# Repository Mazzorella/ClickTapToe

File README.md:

# ClickTapToe

ClickTapToe is a custom foot-operated mouse for people who need to reduce repetitive hand and arm movement. The goal is to move common mouse actions away from the hands by using foot pedals for clicking, a large foot-driven scroll wheel, and a separate mouse pointer module.

This repository contains the firmware, hardware notes, and project documentation for ClickTapToe. The current firmware target is a Seeed Studio XIAO nRF52840 / XIAO BLE running as a USB HID mouse with ZMK. Bluetooth is disabled for the ClickTapToe firmware build.

## Current Status

The current firmware supports USB mouse clicks from external pedals, USB vertical scrolling from the input hub scroll wheel, and pointer movement from the mouse pointer module:

- Left click on the first pedal input
- Right click on the second pedal input
- Vertical scroll from the AS5600 magnetic angle sensor connected to the input hub scroll wheel
- Pointer movement from the PMW3610 sensor in the mouse pointer module
- `D2` and `D3` remain spare/test inputs and are not exposed as production pedal jacks on the current input hub PCB

PMW3610 pointing support is active for the current firmware target.

## Hardware Overview

ClickTapToe is built from two custom electronics modules plus external pedals:

- The input hub contains the XIAO nRF52840 controller, USB connection, external pedal TS jacks, RJ45 pointer connection, and a large foot-operated scroll wheel coupled to an AS5600 magnetic angle sensor.
- The mouse pointer module is shaped like a slipper, houses a PMW3610 pointing sensor, and connects to the input hub over RJ45 with a short Ethernet cable.
- The pedals are premade external pedals connected to the input hub so higher-quality parts can be used and the project is easier to reproduce.

See [HARDWARE.md](HARDWARE.md) for the current pin map and hardware notes.
For a public-facing hardware overview with embedded board previews, open the
[ClickTapToe Hardware Viewer](https://mazzorella.github.io/ClickTapToe/).

| Board | Source | KiCanvas preview |
| --- | --- | --- |
| Input hub | [hardware/input-hub/](hardware/input-hub/) | [Open preview](https://mazzorella.github.io/ClickTapToe/hardware/input-hub/kicanvas.html) |
| Mouse pointer | [hardware/mouse-pointer/](hardware/mouse-pointer/) | [Open preview](https://mazzorella.github.io/ClickTapToe/hardware/mouse-pointer/kicanvas.html) |

## Repository Layout

- `.github/workflows/build.yml` runs the upstream ZMK user-config build workflow.
- `build.yaml` defines the firmware build matrix.
- `config/west.yml` tracks upstream ZMK and imports ZMK's west manifest.
- `zephyr/module.yml` declares this repository as the `zmk-keyboard-clicktaptoe` module and exposes its board, devicetree binding, Kconfig, and driver files.
- `boards/shields/clicktaptoe/` contains the ClickTapToe shield definition, overlay, metadata, and default keymap.
- `Makefile` wraps the local `west build` command for Docker/devcontainer use.
- `hardware/` contains the input hub and mouse pointer KiCad source files.
- `docs/` is reserved for assembly, usage, and release documentation.

## Build Target

The active firmware target is:

```yaml
board: xiao_ble//zmk
shield: clicktaptoe
artifact-name: clicktaptoe_xiao_usb_zmk
```

## Flashing

1. Build the firmware with GitHub Actions or a local ZMK toolchain.
2. Put the XIAO BLE into bootloader mode so it mounts as a UF2 drive.
3. Copy the generated `clicktaptoe_xiao_usb_zmk.uf2` file onto the mounted drive.
4. After the board reboots, connect it to the host over USB.

## Hardware Test

Use a safe desktop target for click testing, such as an empty Finder window or browser page.

- Short physical `D0` to `GND`; the host should receive a left click.
- Short physical `D1` to `GND`; the host should receive a right click.
- Rotate the AS5600 scroll wheel; the host should receive vertical scroll events.
- Move the mouse pointer module over a surface; the host pointer should move smoothly in the same direction.
- Test the PMW3610 once through the RJ45 cable path; pointer response should match the direct breadboard wiring test.
- Leave the AS5600 magnet away from the sensor once as a negative test; the host should not scroll continuously.
- Verify `D2` and `D3` only as spare/test GPIOs if they are wired for bring-up.

If macOS does not immediately recognize the updated HID device, unplug and reconnect the XIAO BLE.
If an old Bluetooth name appears after flashing, remove the cached Bluetooth entry from the host. This firmware build disables ZMK BLE.
If the PMW3610 does not move the pointer after flashing, power-cycle the XIAO once. The input hub physically routes PMW3610 `nRESET` on XIAO `D6` / RJ45 pin 8, but the current firmware still relies on SPI/software reset and does not drive that reset line yet.

## Local Build Notes

This repository is both a ZMK config repository and a ZMK module. Local builds should make the repository visible to ZMK as the config path and as an extra module so the custom `clicktaptoe` shield can be discovered.

The preferred local workflow is to build from a ZMK Docker/devcontainer environment and use this repository's `Makefile`.

One common local layout is to keep this repository next to a ZMK firmware checkout:

```text
projects/
  zmk/
  zmk-pmw3610-driver/
  ClickTapToe/
```

Open the ZMK firmware checkout in VS Code:

```sh
code /path/to/projects/zmk
```

Then use **Dev Containers: Reopen in Container**. If using a devcontainer, bind mount this repository into the container and run the build commands from the ClickTapToe repository directory.

On the first devcontainer launch, initialize the Zephyr workspace from the ZMK checkout:

```sh
west init -l app/
west update
```

Restart the devcontainer after `west update` completes.

Clone the PMW3610 driver module where the `Makefile` can find it. In the default devcontainer layout:

```sh
git clone https://github.com/badjeff/zmk-pmw3610-driver /workspaces/zmk-pmw3610-driver
```

After that, run the build commands from this repository:

```sh
make build
```

To build and copy the generated UF2 into this repository's `firmware/` directory:

```sh
make uf2
```

The copied firmware path is:

```sh
firmware/clicktaptoe_xiao_usb_zmk.uf2
```

Build outputs are written under this repository's ignored `build/` directory,
not under ZMK's `app/` tree.

By default, the `Makefile` expects ZMK's app directory to be available at `../zmk/app`, which matches the sibling directory layout shown above. Override `ZMK_APP` if your checkout path differs:

```sh
make uf2 ZMK_APP=/path/to/zmk/app
```

The wrapped `west` command has this shape:

```sh
west build -d "/path/to/this-repo/build/clicktaptoe" -b "xiao_ble//zmk" -- \
  -DSHIELD=clicktaptoe \
  -DZMK_CONFIG="/path/to/this-repo/config" \
  -DZMK_EXTRA_MODULES="/path/to/this-repo;/path/to/zmk-pmw3610-driver"
```

By default, the `Makefile` expects the PMW3610 driver module at `../zmk-pmw3610-driver`. Override `PMW3610_MODULE` if your checkout path differs:

```sh
make uf2 PMW3610_MODULE=/path/to/zmk-pmw3610-driver
```

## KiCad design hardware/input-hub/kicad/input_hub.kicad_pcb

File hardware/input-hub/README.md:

# Input Hub Hardware

This folder contains source files and notes for the ClickTapToe input hub PCB.

The input hub is the central electronics board. It hosts the XIAO nRF52840,
connects to the computer over USB, receives the external pedal TS jacks,
connects to the mouse pointer board over RJ45, and interfaces with the AS5600
scroll sensor.

## XIAO Pin Test Plan

This validation plan keeps the existing click pedals on `D0`/`D1`, uses the
AS5600 scroll sensor on the `D4`/`D5` I2C bus, and leaves the PMW3610 SPI
signals unchanged.

| XIAO pin | Signal plan | Firmware status |
| --- | --- | --- |
| `D0` | Left click pedal | Implemented |
| `D1` | Right click pedal | Implemented |
| `D2` | Future footswitch / TTS / spare input | Test direct GPIO input, emits play/pause |
| `D3` | Future footswitch / TTS / spare input | Test direct GPIO input, emits volume up |
| `D4` | AS5600 I2C bus | Implemented as `&xiao_i2c` |
| `D5` | AS5600 I2C bus | Implemented as `&xiao_i2c` |
| `D6` | PMW3610 `nRESET` | Implemented as active-low hardware reset |
| `D7` | PMW3610 `MOTION` | Implemented as PMW3610 interrupt |
| `D8` / `P1.13` | PMW3610 `SCLK` | Implemented |
| `D9` / `P1.14` | PMW3610 `nCS` | Implemented |
| `D10` / `P1.15` | PMW3610 `SDIO` | Implemented |

## Mouse Pointer RJ45 Pinout

The mouse pointer connector is an 8P8C modular jack used for ClickTapToe sensor
wiring. It is not Ethernet. The input hub RJ45 wiring must match the mouse
pointer board exactly.

| RJ45 pin | Signal | Input hub side |
| --- | --- | --- |
| 1 | `VIN` / `3V3` | 3.3 V sensor power |
| 2 | `GND` | Ground |
| 3 | `SCLK` | PMW3610 SPI clock |
| 4 | `SDIO` | PMW3610 bidirectional SPI data |
| 5 | `nCS` | PMW3610 chip select |
| 6 | `GND` | Ground |
| 7 | `MOTION` | PMW3610 motion interrupt |
| 8 | `nRESET` | PMW3610 reset routed to XIAO `D6` |

Twisted pair grouping:

| Pair | RJ45 pins | Signals |
| --- | --- | --- |
| Pair 1 | 1-2 | `VIN` / `3V3` + `GND` |
| Pair 2 | 3-6 | `SCLK` + `GND` |
| Pair 3 | 4-5 | `SDIO` + `nCS` |
| Pair 4 | 7-8 | `MOTION` + `nRESET` |

Series resistors for `SCLK`, `SDIO`, `nCS`, and `nRESET` belong on the input hub
side. The mouse pointer board only adds a local 100 ohm series resistor on
`MOTION`, and the input hub provides the `MOTION` pull-up to `3V3`.

`MOTION` is active-low and is handled by firmware on XIAO `D7`; the board also
has a 10k pull-up to `3V3` on that line.
`nRESET` is present in the cable on RJ45 pin 8 and is driven by firmware on XIAO
`D6` during PMW3610 initialization and retry.

## Online Review

`kicanvas.html` embeds the schematic and PCB in KiCanvas for browser-based
review. If GitHub Pages is enabled from the repository root, the input hub
viewer is available at:

```text
https://mazzorella.github.io/ClickTapToe/hardware/input-hub/kicanvas.html
```

## Planned Layout

- `kicad/` for KiCad project source files
- `kicad/production/` for generated Gerbers, drill files, BOMs, and placement files

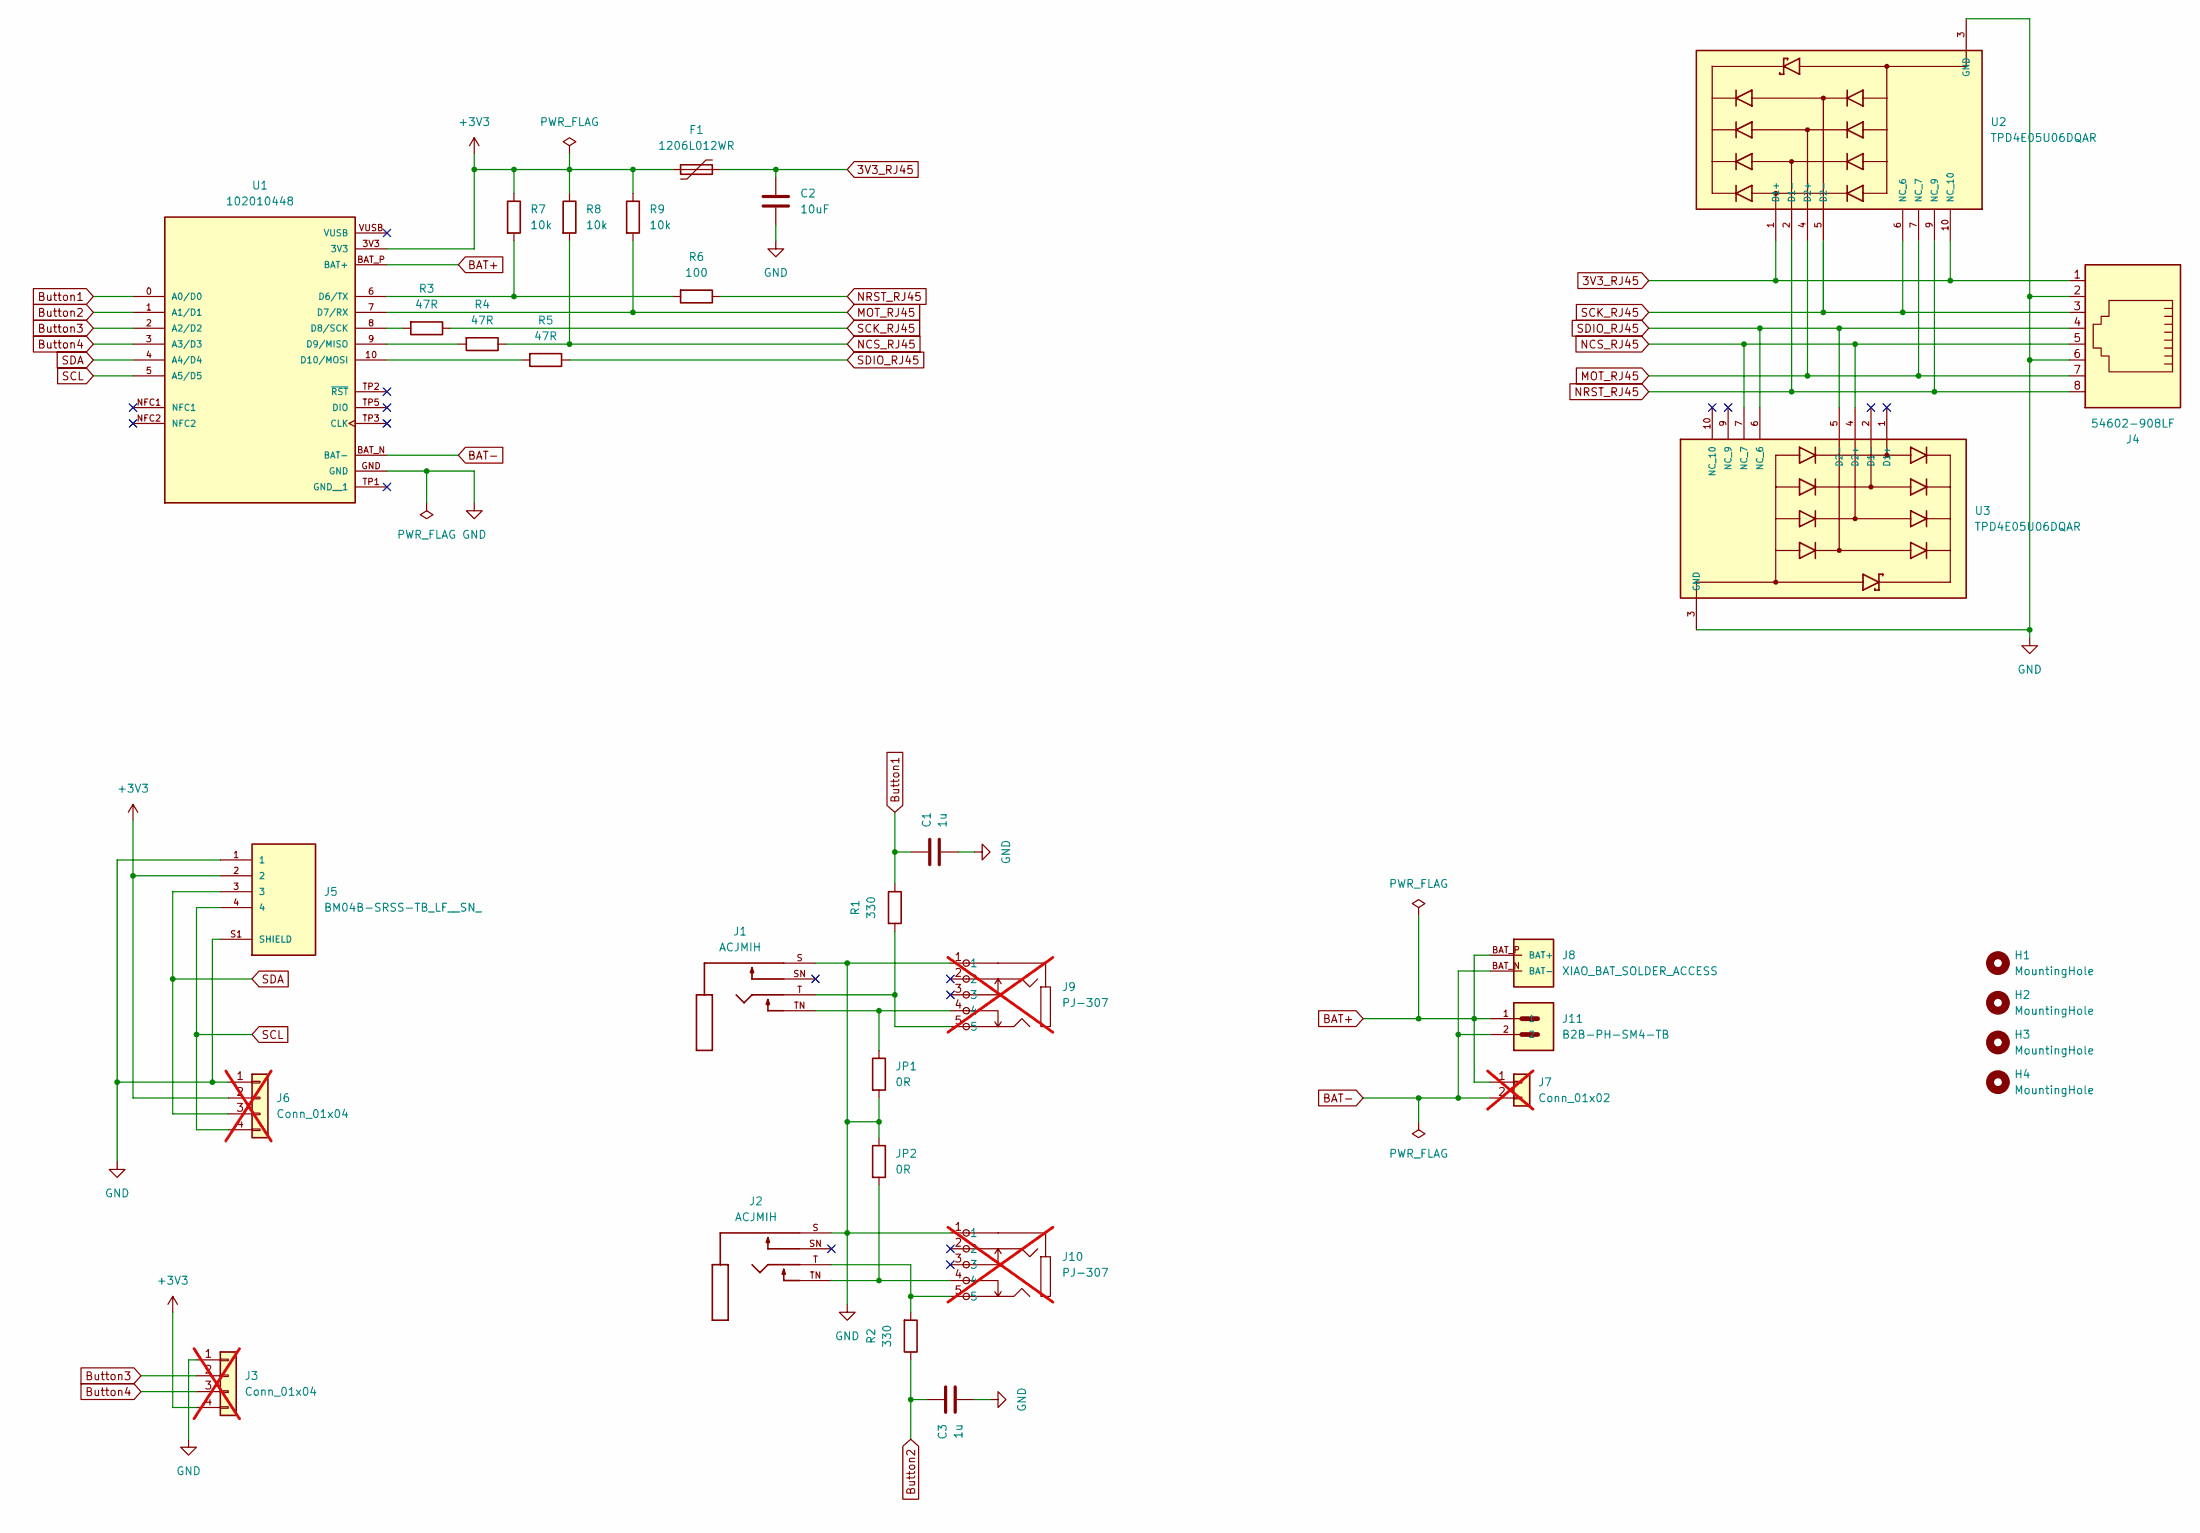
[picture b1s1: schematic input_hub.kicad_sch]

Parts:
C1, C3: 1u; C_0603_1608Metric; JLCPCB Part # C15849
C2: 10uF; C_0805_2012Metric; JLCPCB Part # C15850
F1: 1206L012WR; Fuse_1206_3216Metric; JLCPCB Part # C151160
H1, H2, H3, H4: MountingHole; MountingHole_3.2mm_M3_ISO14580
J1, J2: ACJMIH; AMPHENOL_ACJMIH; PARTREV 2; DigiKey_Part_Number 889-ACJM-IH-ND
J3, J6: Conn_01x04; PinHeader_1x04_P2.54mm_Vertical; not fitted
J4: 54602-908LF; RJ45_Amphenol_54602-x08_Horizontal; MFR. Part # 54602-908LF; Digi-Key MFR. Part # 54602-908LF
J5: BM04B-SRSS-TB_LF__SN_; JST_BM04B-SRSS-TB_LF__SN_; PARTREV N/A; JLCPCB Part # C160390
J7: Conn_01x02; PinHeader_1x02_P2.54mm_Vertical; not fitted
J8: XIAO_BAT_SOLDER_ACCESS
J9, J10: PJ-307; AUDIO-TH_PJ-307; MPN PJ-307; LCSC Part C2939173; not fitted
J11: B2B-PH-SM4-TB; JST_PH_B2B-PH-SM4-TB_1x02-1MP_P2.00mm_Vertical; MFR. Part # B2B-PH-SM4-TB(LF)(SN); JLCPCB Part # C160352
JP1, JP2: 0R; R_0603_1608Metric; JLCPCB Part # C21189
R1, R2: 330; R_0603_1608Metric; JLCPCB Part # C23138
R3, R4, R5: 47R; R_0603_1608Metric; JLCPCB Part # C23182
R6: 100; R_0603_1608Metric; JLCPCB Part # C22775
R7, R8, R9: 10k; R_0603_1608Metric; JLCPCB Part # C25804
U1: 102010448; MODULE_102010448; PARTREV 2022/08/18; Digi-Key MFR. Part # 102010448
U2, U3: TPD4E05U06DQAR; IC_TPD4E05U06DQAR; PARTREV N; JLCPCB Part # C138714

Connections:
3V3_RJ45: C2.2, F1.2, J4.1, U2.1 (D1+), U2.10 (NC_10)
+3V3: F1.1, J3.4, J5.2, J6.2, R7.1, R8.1, R9.1, U1.3V3
BAT+: J7.1, J8.BAT_P (BAT+), J11.1, U1.BAT_P (BAT+)
BAT-: J7.2, J8.BAT_N (BAT-), J11.2, U1.BAT_N (BAT-)
Button1: C1.2, R1.1, U1.0 (A0/D0)
Button2: C3.2, R2.1, U1.1 (A1/D1)
Button3: J3.2, U1.2 (A2/D2)
Button4: J3.3, U1.3 (A3/D3)
GND: C1.1, C2.1, C3.1, J1.S, J2.S, J3.1, J4.2, J4.6, J5.1, J5.S1 (SHIELD), J5.S2 (SHIELD), J6.1, J9.1, J10.1, JP1.2, JP2.1, U1.GND, U2.3 (GND), U2.8 (GND), U3.3 (GND), U3.8 (GND)
MOT_RJ45: J4.7, R9.2, U1.7 (D7/RX), U2.4 (D2+), U2.7 (NC_7)
NCS_RJ45: J4.5, R4.1, R8.2, U3.4 (D2+), U3.7 (NC_7)
NRST_RJ45: J4.8, R6.1, U2.2 (D1-), U2.9 (NC_9)
unnamed: J1.T, J9.5, R1.2
unnamed: J1.TN, J9.4, JP1.1
unnamed: J2.TN, J10.4, JP2.2
unnamed: J2.T, J10.5, R2.2
unnamed: R6.2, R7.2, U1.6 (D6/TX)
unnamed: R3.2, U1.8 (D8/SCK)
unnamed: R4.2, U1.9 (D9/MISO)
unnamed: R5.2, U1.10 (D10/MOSI)
SCK_RJ45: J4.3, R3.1, U2.5 (D2-), U2.6 (NC_6)
SCL: J5.4, J6.4, U1.5 (A5/D5)
SDA: J5.3, J6.3, U1.4 (A4/D4)
SDIO_RJ45: J4.4, R5.1, U3.5 (D2-), U3.6 (NC_6)

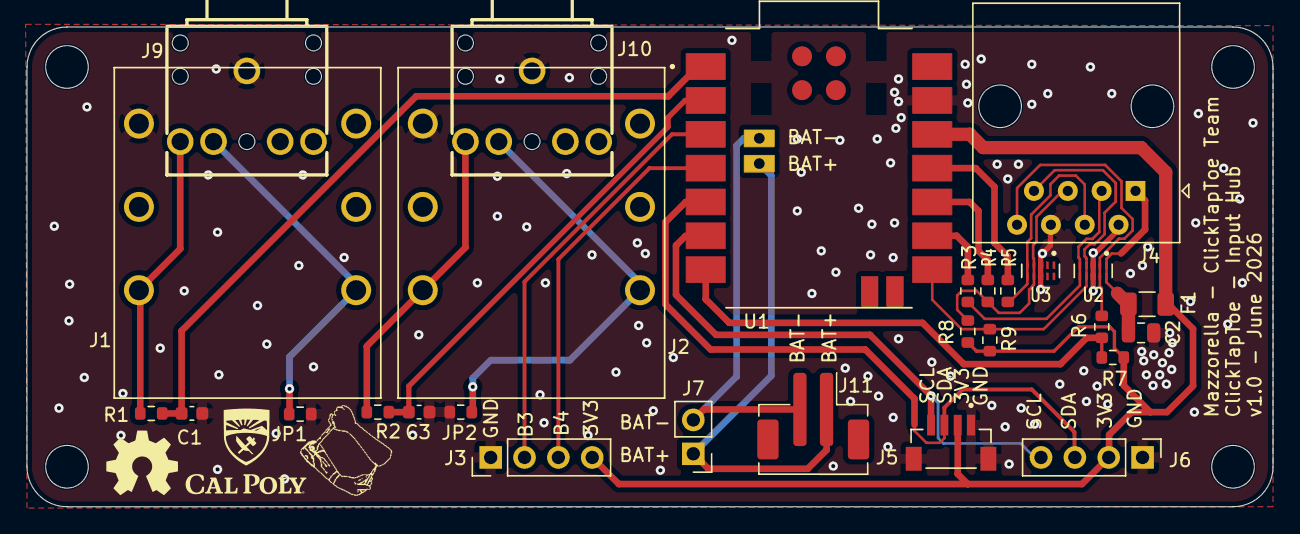
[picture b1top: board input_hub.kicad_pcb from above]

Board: 2 copper layers, 93.5 x 36.0 mm, 33 parts (0 on the bottom side), 24 nets.

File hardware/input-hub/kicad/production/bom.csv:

Designator,Footprint,Quantity,Value,LCSC Part #
"C1, C3",0603,2,1u,C15849
C2,0805,1,10uF,C15850
F1,1206,1,1206L012WR,C151160
J11,JST_PH_B2B-PH-SM4-TB_1x02-1MP_P2.00mm_Vertical,1,B2B-PH-SM4-TB,C160352
J5,JST_BM04B-SRSS-TB_LF__SN_,1,BM04B-SRSS-TB_LF__SN_,C160390
"JP1, JP2",0603,2,0R,C21189
"R1, R2",0603,2,330,C23138
"R3, R4, R5",0603,3,47R,C23182
R6,0603,1,100,C22775
"R7, R8, R9",0603,3,10k,C25804
"U2, U3",IC_TPD4E05U06DQAR,2,TPD4E05U06DQAR,C138714

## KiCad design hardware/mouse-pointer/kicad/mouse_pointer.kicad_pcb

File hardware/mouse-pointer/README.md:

# Mouse Pointer Hardware

This folder contains source files and notes for the ClickTapToe mouse pointer
PCB.

The mouse pointer board contains the optical pointing sensor and connects to the
input hub over RJ45.

The initial KiCad source for this board is derived from the PMW3610 breakout by
`siderakb/pmw3610-pcb`. The current ClickTapToe revision preserves the original
PMW3610 optical/lens/LDO section while adding the project-specific RJ45 cable
interface.

Mouse Pointer 1.0 is the first ClickTapToe-maintained production revision of
this board.

## RJ45 Pinout

The connector is an 8P8C modular jack used for ClickTapToe sensor wiring. It is
not Ethernet.

| RJ45 pin | Signal | Notes |
| --- | --- | --- |
| 1 | `VIN` / `3V3` | Sensor board input power |
| 2 | `GND` | Ground return |
| 3 | `SCLK` | PMW3610 SPI clock |
| 4 | `SDIO` | PMW3610 bidirectional SPI data |
| 5 | `nCS` | PMW3610 chip select |
| 6 | `GND` | Ground return paired with `SCLK` |
| 7 | `MOTION` | Active-low PMW3610 motion output after local series resistor |
| 8 | `nRESET` | Reset routed from the input hub through a 0 ohm link |

Twisted pair grouping:

| Pair | RJ45 pins | Signals |
| --- | --- | --- |
| Pair 1 | 1-2 | `VIN` / `3V3` + `GND` |
| Pair 2 | 3-6 | `SCLK` + `GND` |
| Pair 3 | 4-5 | `SDIO` + `nCS` |
| Pair 4 | 7-8 | `MOTION` + `nRESET` |

## Board Configuration

- Default logic configuration is 3.3 V: `JP1` is a 0 ohm link from `VIN` to
  `VDDIO` and is installed by default.
- Alternate 1.8 V logic is available by populating `JP2`, a 0 ohm link from
  `+1V8` to `VDDIO`. `JP2` is DNP by default.
- `JP3` is a 0 ohm reset link from RJ45 `nRESET` to PMW3610 `nRESET` and is
  installed by default.
- `R3` is a 100 ohm series resistor on `MOTION`, placed near the PMW3610 side
  before the signal leaves the board.
- `R2` is a 100k optional `nCS` pull-up to `VDDIO` and is DNP by default.
- `J1` remains as a debug/test header on the PMW3610-side signals.
- `U3` and `U4` are TPD4E05U06DQAR ESD protection arrays on the RJ45-facing
  cable signals.

The RJ45 connector is unshielded and is intended for hand installation. `J1` is
also optional/test-only and is not assigned a JLCPCB part number in the
production BOM.

The current firmware handles `MOTION` on XIAO `D7` through RJ45 pin 7 and
pulses `nRESET` on XIAO `D6` through RJ45 pin 8 before PMW3610 initialization.

## Online Review

`kicanvas.html` embeds the schematic and PCB in KiCanvas for browser-based
review. If GitHub Pages is enabled from the repository root, the mouse pointer
viewer is available at:

```text
https://mazzorella.github.io/ClickTapToe/hardware/mouse-pointer/kicanvas.html
```

## Planned Layout

- `kicad/` for KiCad project source files
- `production/` for generated Gerbers, drill files, BOMs, and placement files

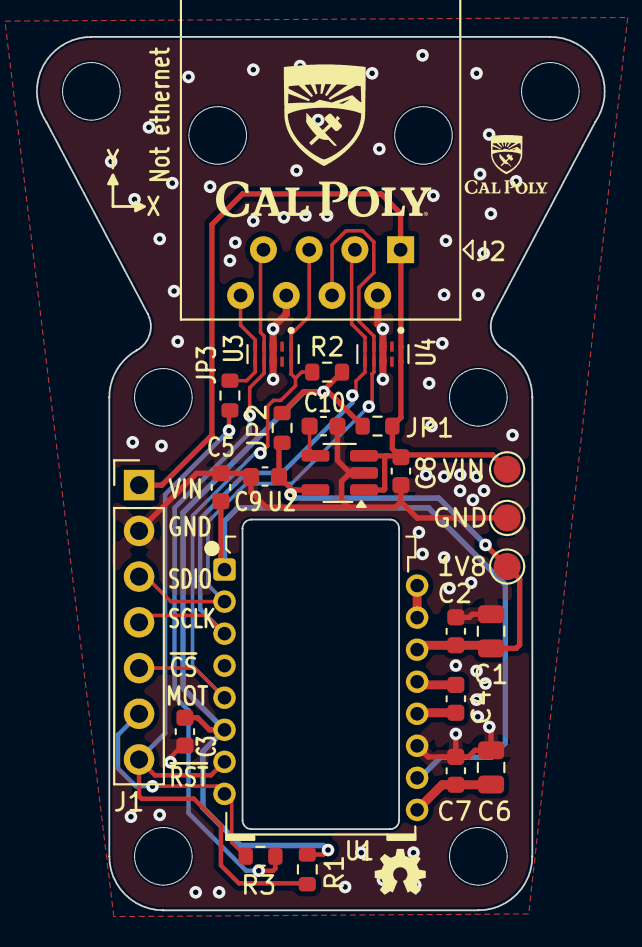
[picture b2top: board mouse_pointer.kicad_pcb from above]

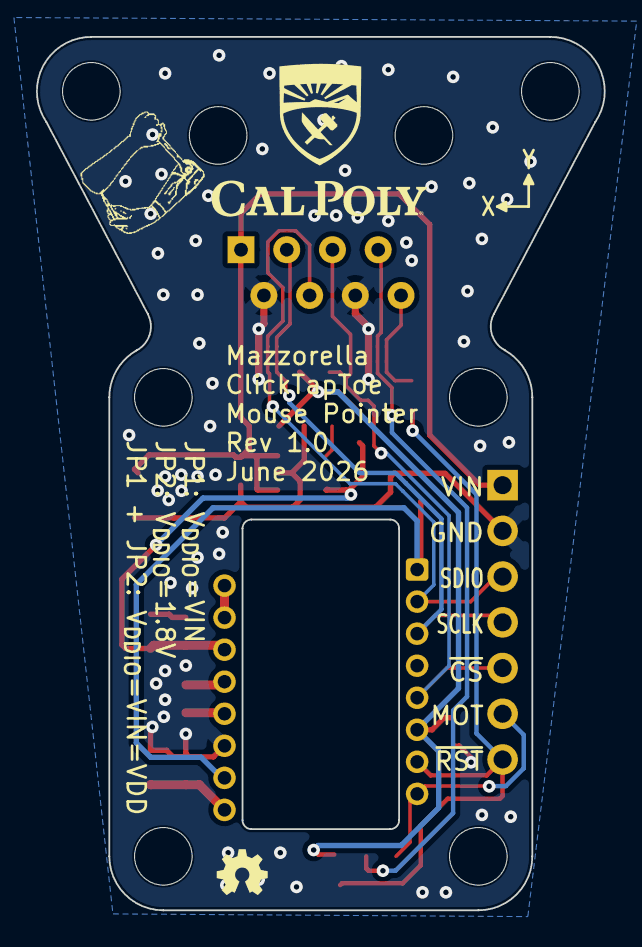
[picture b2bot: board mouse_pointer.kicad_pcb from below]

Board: 2 copper layers, 31.5 x 48.5 mm, 31 parts (3 on the bottom side), 17 nets.

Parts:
C1: 3.3uF/16V; C_0805_2012Metric
C2, C3, C4: 100nF; C_0603_1608Metric
C5, C7: 10nF; C_0603_1608Metric
C6: 10uF; C_0805_2012Metric
C8, C9: 1uF; C_0603_1608Metric
C10: 22nF; C_0603_1608Metric
H1, H2, H3, H4, H5, H6: MountingHole; MountingHole_3.2mm_M3_ISO14580
J1: Conn_PinHeader; PinHeader_1x07_P2.54mm_Vertical
J2: 54602-908LF; RJ45_Amphenol_54602-x08_Horizontal
JP1, JP2, JP3: 0R; R_0603_1608Metric
R1: 10k; R_0603_1608Metric
R2: 100k; R_0603_1608Metric
R3: 100; R_0603_1608Metric
TP1, TP2, TP3: TestPoint; TestPoint_Pad_D1.5mm
U1: PMW3610; PMW3610DM-SUDU 16Pin
U2: TLV74318PDBVR; SOT-23-5_HandSoldering
U3, U4: TPD4E05U06DQAR; IC_TPD4E05U06DQAR

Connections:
+1V8: C1.1, C2.1, C9.1, JP2.2, TP3.1 (1_1), U1.14 (VDD), U2.5 (OUT)
GND: C1.2, C2.2, C3.2, C5.2, C6.2, C7.2, C8.2, C9.2, C10.2, J1.2, J2.2, J2.6, TP2.1 (1_1), U1.11 (GND), U2.2 (GND), U3.3 (GND), U3.8 (GND), U4.3 (GND), U4.8 (GND)
MOTION: J1.6, R3.1, U1.8 (MOTION)
MOT_RJ45: J2.7, R3.2, U3.4 (D2+), U3.7 (NC_7)
unnamed: C5.1, U1.1 (+VCSEL), U1.10 (PASS_T)
unnamed: U1.15 (XYLASER), U1.16 (-VCSEL)
unnamed: C4.2, U1.13 (CN)
unnamed: C4.1, U1.12 (CP)
unnamed: C6.1, C7.1, U1.9 (VCP)
unnamed: C10.1, U2.4 (NC)
SCLK: J1.4, J2.3, U1.3 (SCLK), U4.5 (D2-), U4.6 (NC_6)
SDIO: J1.3, J2.4, U1.2 (SDIO), U4.4 (D2+), U4.7 (NC_7)
VDDIO: C3.1, JP1.2, JP2.1, R1.1, R2.1, U1.6 (VDDIO)
VIN: C8.1, J1.1, J2.1, JP1.1, TP1.1 (1_1), U2.1 (IN), U2.3 (EN), U4.1 (D1+), U4.10 (NC_10)
nCS: J1.5, J2.5, R2.2, U1.5 (NCS), U3.1 (D1+), U3.10 (NC_10)
nRESET: J1.7, JP3.1, R1.2, U1.7 (NRESET)
nRST_RJ45: J2.8, JP3.2, U3.5 (D2-), U3.6 (NC_6)

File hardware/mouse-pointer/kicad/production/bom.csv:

Designator,Footprint,Quantity,Value,LCSC Part #
C1,0805,1,3.3uF/16V,C7393948
"C2, C3, C4",0603,3,100nF,C14663
"C5, C7",0603,2,10nF,C57112
C6,0805,1,10uF,C15850
"C8, C9",0603,2,1uF,C15849
"JP1, JP3",0603,2,0R,C21189
R1,0603,1,10k,C25804
R3,0603,1,100,C22775
U1,PMW3610DM-SUDU 16Pin,1,PMW3610,C42442560
U2,SOT-23-5_HandSoldering,1,TLV74318PDBVR,C485152
"U3, U4",IC_TPD4E05U06DQAR,2,TPD4E05U06DQAR,C138714

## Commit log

2026-04-29 Initial commit with repo set up, zmk config, and working left and right click
2026-04-29 Add EC11 scroll wheel firmware functionality
2026-04-29 Tune Github language detection
2026-04-30 Implemented PMW3610 for mouse pointing, disabled bluetooth, checked functionality with ethernet cable
2026-05-14 chore: standardize project workflow and hardware structure
    - Rename hardware
    folders around input-hub and mouse-pointer boards.
    - Add hardware placeholder structure for
    source and production outputs.
    - Add CONTRIBUTING.md with commit, branch, release, and changelog
    conventions.
2026-05-14 feat: import mouse pointer board baseline
    - Import the cleaned PMW3610 KiCad
    project as the mouse-pointer board baseline.
    - Rename KiCad project files and local symbol/
    footprint libraries to use mouse_pointer naming.
    - Preserve the upstream CERN-OHL-P v2 license
    and attribution notice.
2026-05-14 chore: refresh standard KiCad library footprints
    - Update standard
    passive, mounting hole, regulator, and header footprints from the KiCad 10 libraries.
    - Preserve
    custom mouse-pointer footprints and JLC assembly metadata.
2026-05-14 fix: resolve mouse pointer schematic ERC errors
    - Correct PMW3610 internal
    support pin electrical types.
    - Add power flags for VIN, GND, and VDDIO.
2026-05-14 chore: refresh standard KiCad schematic symbols
    - Update standard resistor
    and solder jumper symbols from the KiCad 10 libraries.
    - Exclude solder jumpers from the BOM
    because they are PCB copper features, not assembled parts.
    - Preserve schematic fields and JLC
    assembly metadata.
2026-05-14 feat: add RJ45 mouse pointer board interface
    - Add the ClickTapToe 8P8C/RJ45 pinout to the PMW3610 mouse pointer board.
    - Add reset and VDDIO configuration links, optional nCS pull-up, and MOTION series resistor.
    - Extend the board layout for the RJ45 connector and added mounting holes.
    - Document revised mouse pointer cabling, twisted-pair grouping, and input hub wiring contract.
2026-05-14 docs: add mouse pointer KiCanvas viewer
    - Add a browser-based KiCanvas page for reviewing the mouse pointer schematic and PCB.
    - Document the GitHub Pages URL for sharing the board preview.
2026-05-18 feat: validate input hub pin reassignment
    - Move the EC11 scroll encoder from D2/D3 to D4/D5.
    - Add D2/D3 as test GPIO inputs for play/pause and volume up.
    - Reserve D6 for PMW3610 nRESET without wiring it into firmware.
    - Keep PMW3610 SPI pins unchanged and document the test pin plan.
    - Move local ZMK build output under this repo to avoid stale app builds.
2026-05-18 fix: calibrate scroll encoder for PEC11R
    - Set EC11 steps for the PEC11R-4215F-S0024 quadrature transition count.
    - Trigger scroll once per 24-detent rotation step.
    - Document the selected encoder part and ZMK calibration values.
2026-05-18 fix: refine mouse pointer board layout
    - Adjust board outline edges.
    - Reposition components for improved decoupling
    - Tune trace routing and via placement
2026-05-18 feat: add input hub board draft
    - Add the XIAO nRF52840 input hub KiCad
    project.
    - Route the PMW3610 RJ45 interface with ESD protection and source-side series parts.
    - Add EC11 and AS5600 scroll input options plus pedal, footswitch, and battery connectors.
    - Include local symbols, footprints, 3D models, and JLC/DigiKey sourcing fields.
2026-05-21 fix: refine input hub board draft
    Update the input hub KiCad design after
    layout review.
    - Replace solder fallback headers with standard 2.54 mm footprints.
    - Clean up PMW3610 RJ45 routing, ESD placement, and local power conditioning.
    - Add optional SJ1-3523N 3.5 mm jack library assets for future pedal jack variants.
    - Preserve AS5600, EC11, footswitch, battery, and PMW3610 interface options for review.
2026-05-21 fix: refine input hub battery layout
    - Update the battery connector layout.
    - Rename the battery connector from P to J.
    - Add return vias near signal vias.
    - Widen power-path traces.
    - Add XIAO battery solder holes and silkscreen labels.
2026-05-22 fix: make input hub routing more gooder and a schematic change - esd routing and schematic - PEC11R debounce circuit - reduced back side routing - added filter caps to 1/4 inch jacks - made traces th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
2026-05-29 feat: add AS5600 scroll sensor support
    - Add a ClickTapToe AS5600 scroll driver for ZMK rotation events.
    - Replace the EC11 scroll path with AS5600 over the XIAO I2C bus.
    - Update hardware and build docs for the magnetic scroll wheel.
2026-05-29 feat: add ESD protection to mouse pointer and update board fields
    - Add ESD protection, logo artwork, and final board manufacturing fields.
    - Include generated fabrication outputs for direct ordering.
    - Document hand-installed RJ45, optional tester header, and board configuration.
2026-05-30 feat: add PJ-307 alternate pedal jacks
    - Import the HOOYA PJ-307/C2939173 symbol, footprint, and STEP model.
    - Replace the stale SJ1-3523N library assets with the PJ-307 part.
    - Add 3.5 mm alternate pedal jack footprints under the 1/4 in pedal jacks.
    - Update silkscreen labels and artwork
2026-06-01 feat: remove input hub EC11 encoder and update 3D models
    - Remove the EC11 encoder and supporting debounce network from the input hub.
    - Add project-local 3D model links for imported input hub footprints.
    - Vendor the RJ45 footprint with the exact Amphenol 54602-908LF model.
    - Add the XIAO battery solder access symbol and footprint.
2026-06-01 feat: remove third TS jack and make vertical JST battery connector
    - Remove the third pedal jack option to reduce board width.
    - Align edge connectors for a cleaner enclosure-facing layout.
    - Replace the horizontal battery JST with a vertical B2B-PH-SM4-TB footprint.
    - Remove stale horizontal JST symbol, footprint, and model assets.
2026-06-02 docs: clarify PMW3610 reset and motion routing
    - Document MOTION on XIAO D7
    and RJ45 pin 7 as the implemented PMW3610 interrupt.
    - Document nRESET on XIAO D6 and RJ45 pin 8 as physically routed but not firmware-driven yet.
    - Remove stale third pedal jack and unrouted reset references from bring-up notes.
    - Keep the input hub, mouse pointer, hardware map, and overlay comments in sync.
2026-06-02 feat: updated board for JLC constraints, add 3D models, add silkscreen logos, correct production outputs
    - Add Cal Poly and EMPOWER silkscreen artwork and generated KiCad footprints.
    - Add PMW3610 and RJ45 model assets for board review.
    - Update JLC board constraints and clean up resulting DRC issues.
    - Update ESD placement rotation fields for JLC assembly output.
    - Exclude optional headers, RJ45s, DNP parts, test points, and holes from assembly files.
    - Regenerate mouse pointer production BOM, CPL, netlist, and fabrication archive.
2026-06-02 chore: set mouse pointer board revision to 1.0
    - Mark Mouse Pointer 1.0 as the first ClickTapToe-maintained production revision.
    - Replace the old Mouse_Pointer_3.0 fabrication archive with Mouse_Pointer_1.0.
    - Update hardware notes for the current reset routing and firmware behavior.
2026-06-03 feat: prep input hub for JLC assembly
    - Add JLC-oriented board constraints, DRC exclusions, revised vias, and production metadata.
    - Add input hub 3D model links, silkscreen logos, PJ-307 footprint updates, and vertical battery
    JST metadata.
    - Route/document PMW3610 reset and MOTION pull-up support with firmware retry configuration.
    - Clean up remaining EC11 encoder library artifacts and stale encoder nets.
2026-06-11 fix: validate working config with input hub PCB
    Validated the input hub PCB
    with the current PMW3610 cable pinout, series resistors, and MOT pull-up using the original SPI
    reset driver path.
    - Switch pedal GPIOs to active-high for normally-closed Yamaha-style pedals.
    - Document the PCB-validated PMW3610 wiring and D6 reset routing.
    - Leave PMW3610 hardware reset/retry firmware work out of this checkpoint.
2026-06-11 feat: add XIAO onboard status activity LED
    - Use the XIAO BLE onboard RGB LED
    for firmware health and activity status.
    - Show green when AS5600 and PMW3610 health checks pass.
    - Blink red when a required device is missing or unresponsive.
    - Pulse blue for pedal, scroll, and pointer activity.
2026-06-11 feat: add input hub KiCanvas preview
    - Add a KiCanvas preview page for the
    input hub KiCad project.
    - Link both hardware board previews from the main README.
    - Document the input hub preview URL in the board README.
    - Note the next input hub pedal jack normal-contact grounding improvement.
2026-06-11 feat: add public hardware viewer page
    - Add a GitHub Pages hardware viewer
    with board images, KiCanvas embeds, downloads, and assembly guidance.
    - Export static SVG previews for the input hub and mouse pointer boards.
    - Add a combined electronics BOM CSV for one complete board set.
    - Link the public viewer from the main README.
2026-06-11 docs: prep hardware branch for main merge
    - Summarize the merge-ready
    firmware, hardware, and documentation work in the changelog.
    - Add next-step notes for the deferred PMW3610 reset-retry driver stash.
    - Note the stashed XIAO battery access footprint for a future input hub hardware update.
    - Track the tested ClickTapToe UF2 while keeping local build outputs ignored.
    - Clean up README references for the current firmware and tracked firmware artifact.
2026-06-11 chore: tune GitHub language detection
    - Mark KiCad hardware source files as
    detectable for GitHub Linguist.
    - Exclude generated hardware previews, production outputs, 3D models, and firmware artifacts from
    language stats.
2026-06-11 chore: refine GitHub language detection
    - Count KiCad board and schematic
    files in GitHub Linguist.
    - Treat inherited KiCad footprint and symbol libraries as vendored support files.
    - Keep generated exports and firmware artifacts out of language stats.
2026-06-16 fix: add input hub pedal normal jumpers
    - Route pedal jack normal contacts
    through optional 0R jumpers to ground.
    - Use existing 0603 0R jumper sourcing for the new input hub build options.
    - Track release-ready input hub fabrication outputs for ordering.

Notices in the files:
hardware/mouse-pointer/kicad/mouse_pointer.kicad_pcb:
Open Source Hardware, CERN-OHL-P v2
